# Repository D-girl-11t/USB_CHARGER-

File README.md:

# USB_CHARGER-
EAGLE PCB DESIGNING

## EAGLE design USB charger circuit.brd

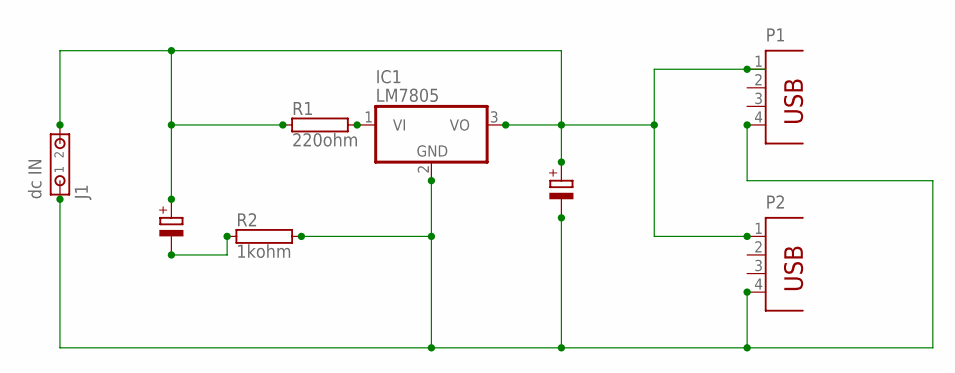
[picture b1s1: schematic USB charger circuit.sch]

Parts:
IC1: LM7805; TO220H
J1: dc IN; 794681-2
P1, P2: PN87520
R1: 220ohm; AC01
R2: 1kohm; AC01

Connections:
unnamed: IC1.1 (VI), R1.2
unnamed: IC1.3 (VO), J1.2, P1.1, P2.1, R1.1
unnamed: IC1.2 (GND), J1.1, P1.4, P2.4, R2.2

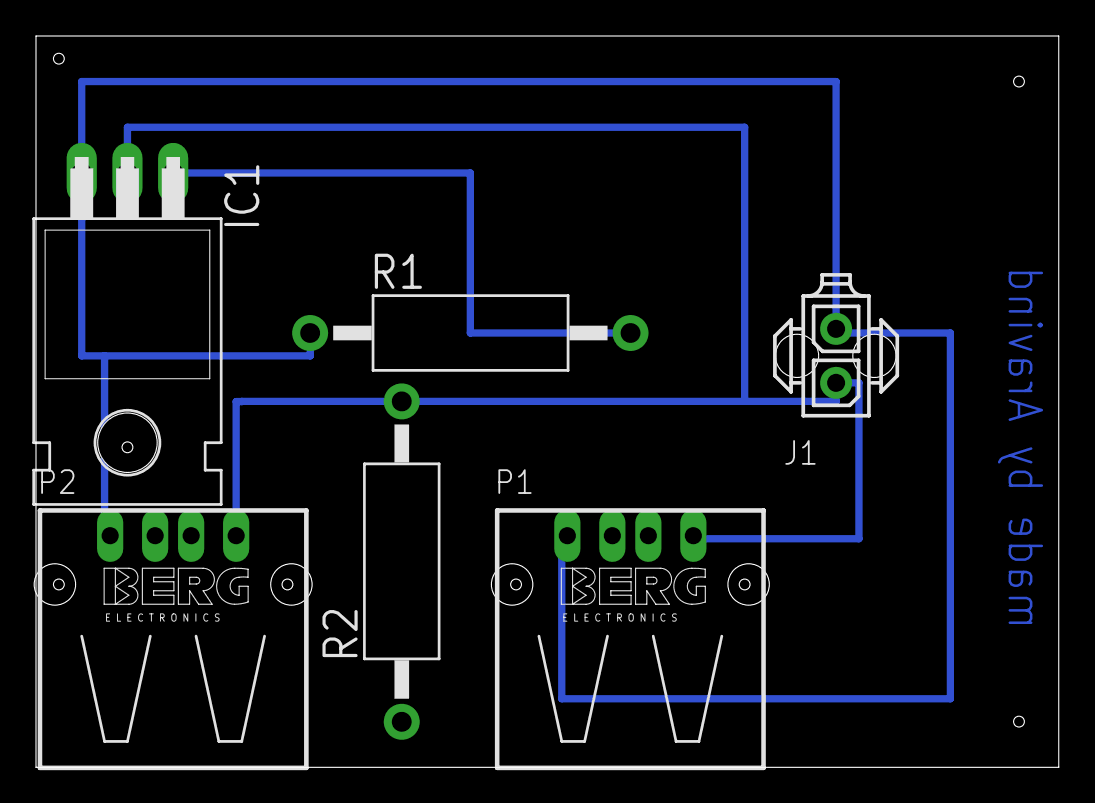
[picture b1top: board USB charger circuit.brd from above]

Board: 2 copper layers, 56.8 x 40.6 mm, 6 parts (0 on the bottom side), 3 nets.
